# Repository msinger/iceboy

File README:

iceboy
------

http://iceboy.a-singer.de/
https://github.com/msinger/iceboy/
https://sourceforge.net/projects/iceboy/

Licensed under CERN-OHL-W v2
https://cern-ohl.web.cern.ch/

The goal of this project is to implement a GameBoy in Verilog using the open
source IceStorm tools for Lattice iCE40HX-8K FPGAs. You can get the tools from
here:
  http://www.clifford.at/icestorm/

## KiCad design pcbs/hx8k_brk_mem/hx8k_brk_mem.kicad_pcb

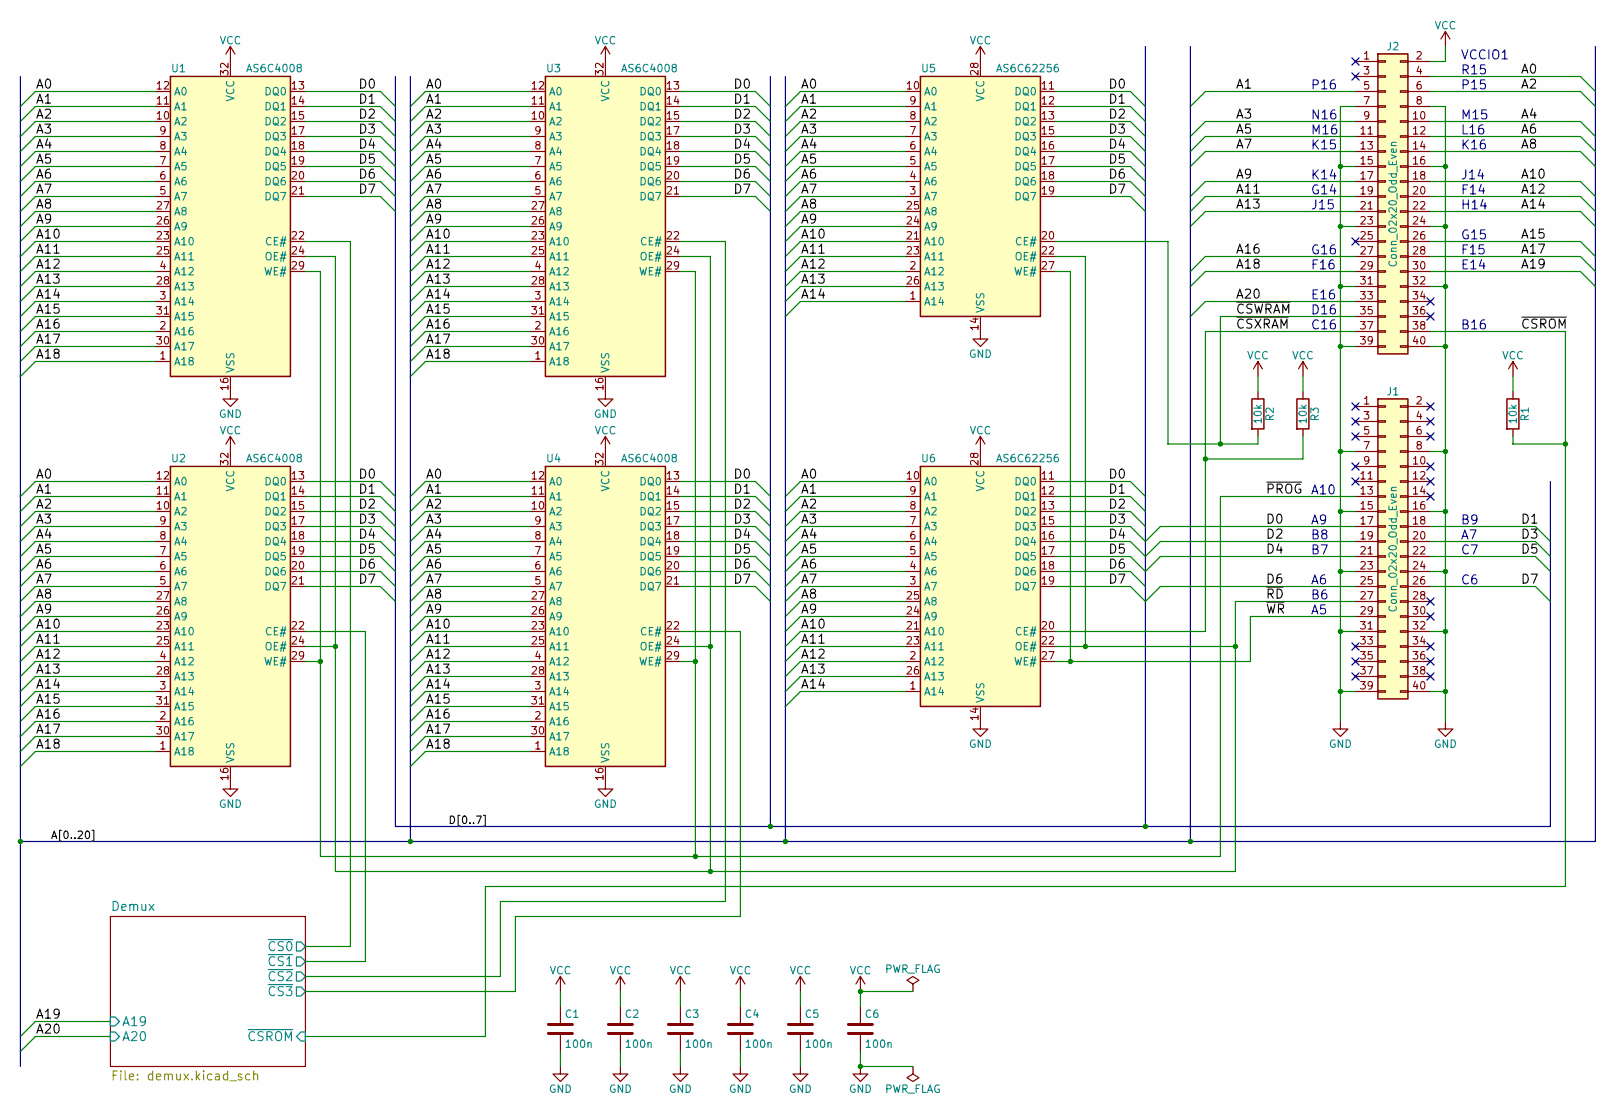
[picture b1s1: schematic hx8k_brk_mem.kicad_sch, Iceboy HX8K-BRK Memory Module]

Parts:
C1, C2, C3, C4, C5, C6: 100n; C_Disc_D3.0mm_W2.0mm_P2.50mm
J1, J2: Conn_02x20_Odd_Even; PinSocket_2x20_P2.54mm_Vertical
R1, R2, R3: 10k; R_Axial_DIN0207_L6.3mm_D2.5mm_P10.16mm_Horizontal
U1, U2, U3, U4: AS6C4008; DIP-32_W15.24mm_Socket
U5, U6: AS6C62256; DIP-28_W15.24mm_Socket

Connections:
/A0: J2.4, U1.12 (A0), U2.12 (A0), U3.12 (A0), U4.12 (A0), U5.10 (A0), U6.10 (A0)
/A1: J2.5, U1.11 (A1), U2.11 (A1), U3.11 (A1), U4.11 (A1), U5.9 (A1), U6.9 (A1)
/A2: J2.6, U1.10 (A2), U2.10 (A2), U3.10 (A2), U4.10 (A2), U5.8 (A2), U6.8 (A2)
/A3: J2.9, U1.9 (A3), U2.9 (A3), U3.9 (A3), U4.9 (A3), U5.7 (A3), U6.7 (A3)
/A4: J2.10, U1.8 (A4), U2.8 (A4), U3.8 (A4), U4.8 (A4), U5.6 (A4), U6.6 (A4)
/A5: J2.11, U1.7 (A5), U2.7 (A5), U3.7 (A5), U4.7 (A5), U5.5 (A5), U6.5 (A5)
/A6: J2.12, U1.6 (A6), U2.6 (A6), U3.6 (A6), U4.6 (A6), U5.4 (A6), U6.4 (A6)
/A7: J2.13, U1.5 (A7), U2.5 (A7), U3.5 (A7), U4.5 (A7), U5.3 (A7), U6.3 (A7)
/A8: J2.14, U1.27 (A8), U2.27 (A8), U3.27 (A8), U4.27 (A8), U5.25 (A8), U6.25 (A8)
/A9: J2.17, U1.26 (A9), U2.26 (A9), U3.26 (A9), U4.26 (A9), U5.24 (A9), U6.24 (A9)
/A10: J2.18, U1.23 (A10), U2.23 (A10), U3.23 (A10), U4.23 (A10), U5.21 (A10), U6.21 (A10)
/A11: J2.19, U1.25 (A11), U2.25 (A11), U3.25 (A11), U4.25 (A11), U5.23 (A11), U6.23 (A11)
/A12: J2.20, U1.4 (A12), U2.4 (A12), U3.4 (A12), U4.4 (A12), U5.2 (A12), U6.2 (A12)
/A13: J2.21, U1.28 (A13), U2.28 (A13), U3.28 (A13), U4.28 (A13), U5.26 (A13), U6.26 (A13)
/A14: J2.22, U1.3 (A14), U2.3 (A14), U3.3 (A14), U4.3 (A14), U5.1 (A14), U6.1 (A14)
/A15: J2.26, U1.31 (A15), U2.31 (A15), U3.31 (A15), U4.31 (A15)
/A16: J2.27, U1.2 (A16), U2.2 (A16), U3.2 (A16), U4.2 (A16)
/A17: J2.28, U1.30 (A17), U2.30 (A17), U3.30 (A17), U4.30 (A17)
/A18: J2.29, U1.1 (A18), U2.1 (A18), U3.1 (A18), U4.1 (A18)
/A19: J2.30; also elsewhere on the board
/A20: J2.33; also elsewhere on the board
/D0: J1.17, U1.13 (DQ0), U2.13 (DQ0), U3.13 (DQ0), U4.13 (DQ0), U5.11 (DQ0), U6.11 (DQ0)
/D1: J1.18, U1.14 (DQ1), U2.14 (DQ1), U3.14 (DQ1), U4.14 (DQ1), U5.12 (DQ1), U6.12 (DQ1)
/D2: J1.19, U1.15 (DQ2), U2.15 (DQ2), U3.15 (DQ2), U4.15 (DQ2), U5.13 (DQ2), U6.13 (DQ2)
/D3: J1.20, U1.17 (DQ3), U2.17 (DQ3), U3.17 (DQ3), U4.17 (DQ3), U5.15 (DQ3), U6.15 (DQ3)
/D4: J1.21, U1.18 (DQ4), U2.18 (DQ4), U3.18 (DQ4), U4.18 (DQ4), U5.16 (DQ4), U6.16 (DQ4)
/D5: J1.22, U1.19 (DQ5), U2.19 (DQ5), U3.19 (DQ5), U4.19 (DQ5), U5.17 (DQ5), U6.17 (DQ5)
/D6: J1.25, U1.20 (DQ6), U2.20 (DQ6), U3.20 (DQ6), U4.20 (DQ6), U5.18 (DQ6), U6.18 (DQ6)
/D7: J1.26, U1.21 (DQ7), U2.21 (DQ7), U3.21 (DQ7), U4.21 (DQ7), U5.19 (DQ7), U6.19 (DQ7)
/Demux/~CS0: U1.22 (CE#); also elsewhere on the board
/Demux/~CS1: U2.22 (CE#); also elsewhere on the board
/Demux/~CS2: U3.22 (CE#); also elsewhere on the board
/Demux/~CS3: U4.22 (CE#); also elsewhere on the board
/~CSROM: J2.38, R1.2; also elsewhere on the board
/~CSWRAM: J2.35, R2.2, U5.20 (CE#)
/~CSXRAM: J2.37, R3.2, U6.20 (CE#)
/~PROG: J1.13, U1.29 (WE#), U2.29 (WE#), U3.29 (WE#), U4.29 (WE#)
/~RD: J1.27, U1.24 (OE#), U2.24 (OE#), U3.24 (OE#), U4.24 (OE#), U5.22 (OE#), U6.22 (OE#)
/~WR: J1.29, U5.27 (WE#), U6.27 (WE#)
GND: C1.2, C2.2, C3.2, C4.2, C5.2, C6.2, J1.7, J1.8, J1.15, J1.16, J1.23, J1.24, J1.31, J1.32, J1.39, J1.40, J2.7, J2.8, J2.15, J2.16, J2.23, J2.24, J2.31, J2.32, J2.39, J2.40, U1.16 (VSS), U2.16 (VSS), U3.16 (VSS), U4.16 (VSS), U5.14 (VSS), U6.14 (VSS); also elsewhere on the board
VCC: C1.1, C2.1, C3.1, C4.1, C5.1, C6.1, J2.2, R1.1, R2.1, R3.1, U1.32 (VCC), U2.32 (VCC), U3.32 (VCC), U4.32 (VCC), U5.28 (VCC), U6.28 (VCC); also elsewhere on the board

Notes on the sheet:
E16
P16
VCCIO1
M15
L16
N16
C16
G16
F16
K16
F15
G14
A10
K15
D16
F14
J15
G15
J14
E14
B16
R15
K14
M16
H14
P15

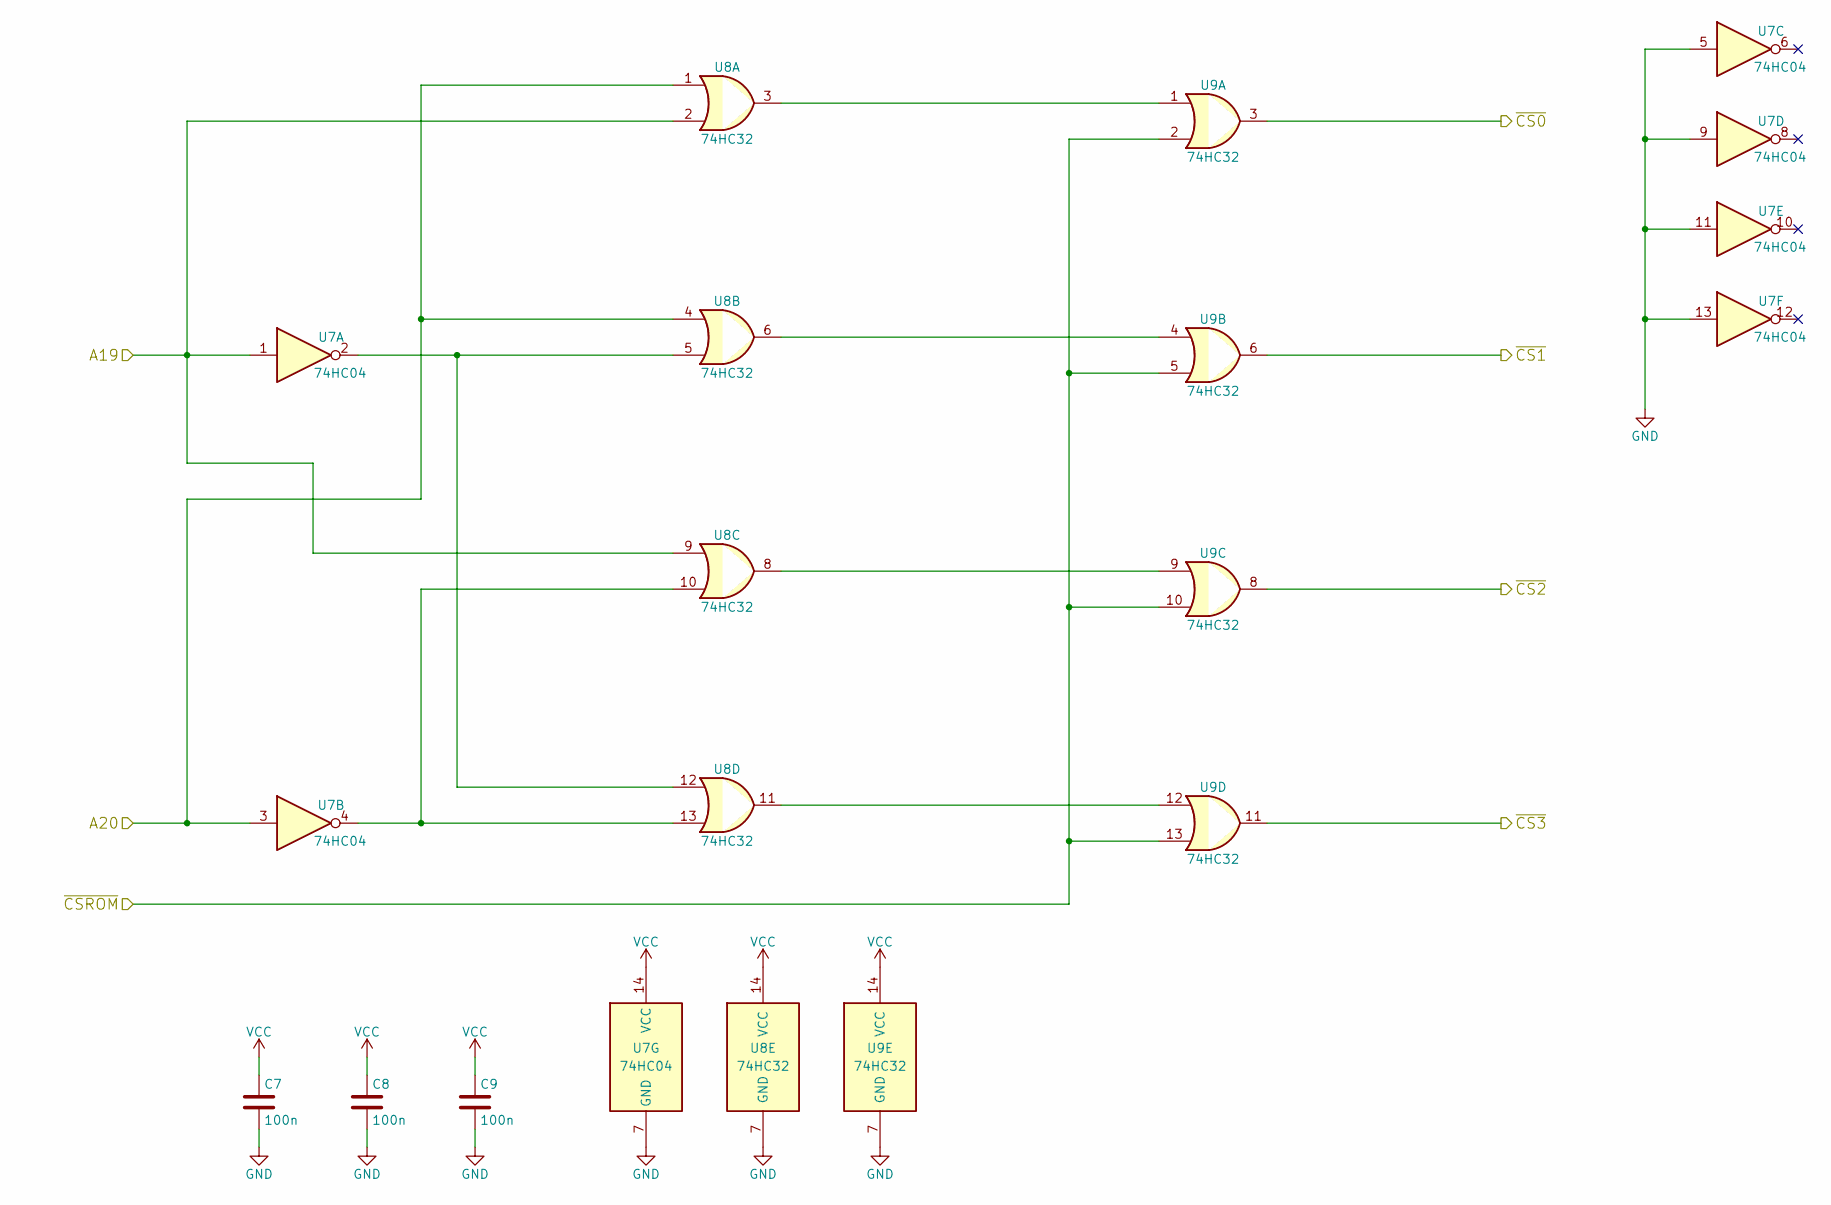
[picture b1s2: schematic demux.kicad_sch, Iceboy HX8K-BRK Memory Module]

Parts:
C7, C8, C9: 100n; C_Disc_D3.0mm_W2.0mm_P2.50mm
U7: 74HC04; DIP-14_W7.62mm_Socket
U8, U9: 74HC32; DIP-14_W7.62mm_Socket

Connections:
/A19: U7.1, U8.2, U8.9; also elsewhere on the board
/A20: U7.3, U8.1, U8.4; also elsewhere on the board
/Demux/~CS0: U9.3; also elsewhere on the board
/Demux/~CS1: U9.6; also elsewhere on the board
/Demux/~CS2: U9.8; also elsewhere on the board
/Demux/~CS3: U9.11; also elsewhere on the board
/~CSROM: U9.2, U9.5, U9.10, U9.13; also elsewhere on the board
GND: C7.2, C8.2, C9.2, U7.5, U7.7 (GND), U7.9, U7.11, U7.13, U8.7 (GND), U9.7 (GND); also elsewhere on the board
unnamed: U7.2, U8.5, U8.12
unnamed: U7.4, U8.10, U8.13
unnamed: U8.3, U9.1
unnamed: U8.6, U9.4
unnamed: U8.8, U9.9
unnamed: U8.11, U9.12
VCC: C7.1, C8.1, C9.1, U7.14 (VCC), U8.14 (VCC), U9.14 (VCC); also elsewhere on the board

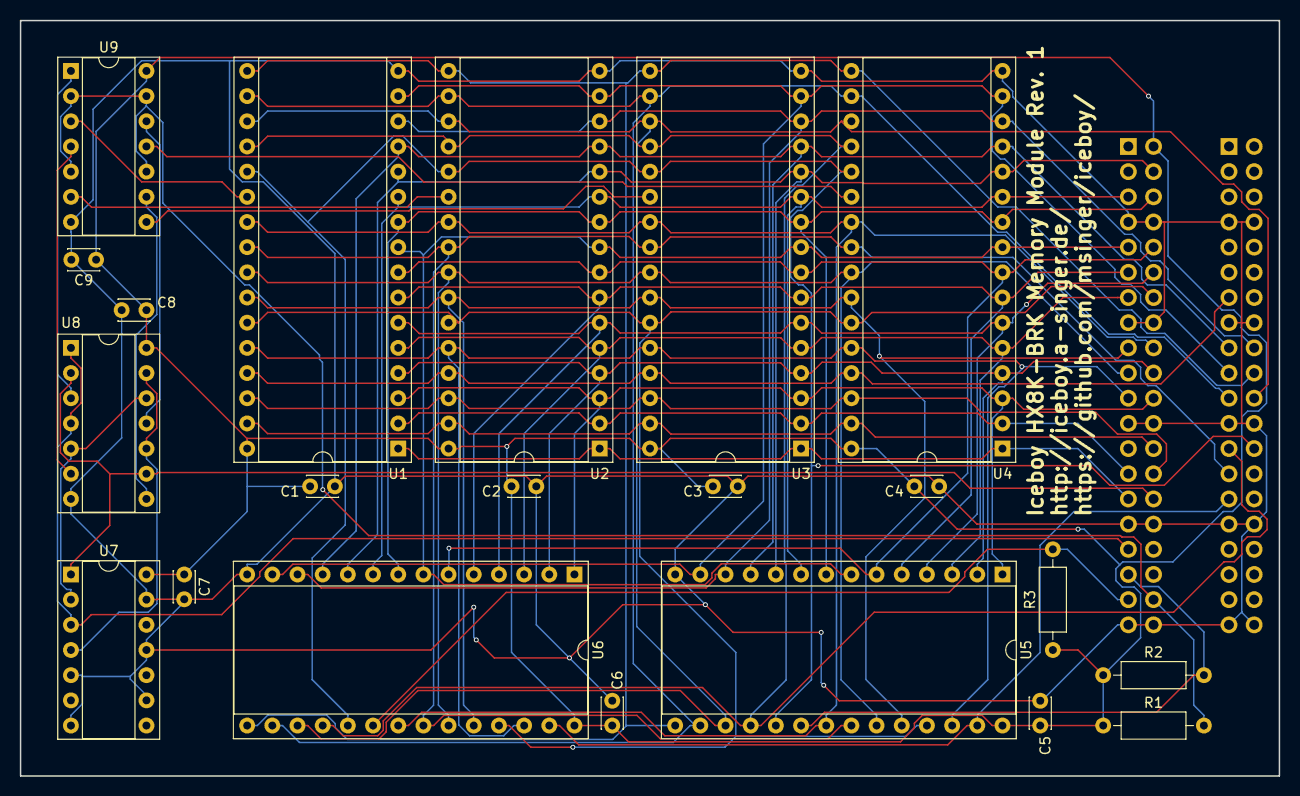
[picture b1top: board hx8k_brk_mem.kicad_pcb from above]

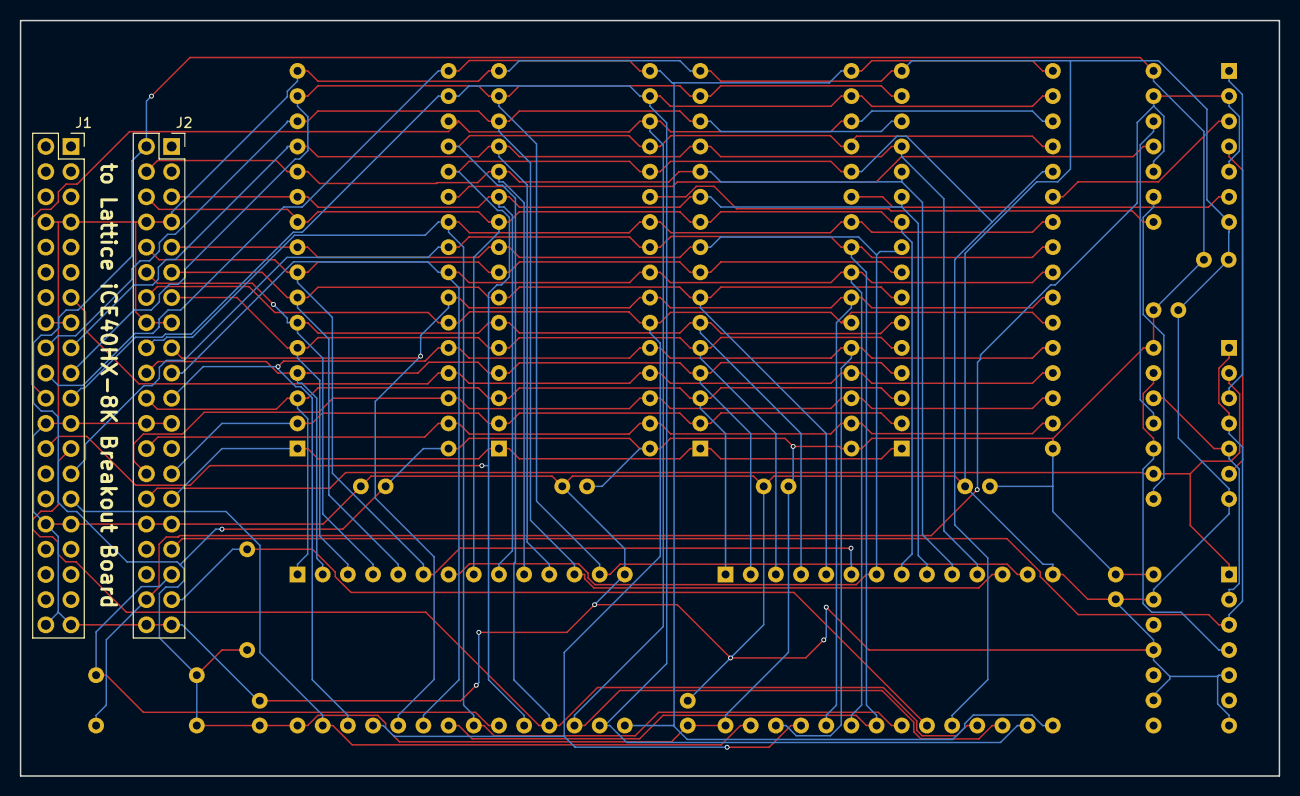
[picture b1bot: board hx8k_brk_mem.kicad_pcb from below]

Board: 2 copper layers, 127.0 x 76.2 mm, 23 parts (2 on the bottom side), 47 nets.

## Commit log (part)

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2018-01-25 add gitignore
2018-01-25 cleanup
2018-01-25 implement more jumps
2018-01-27 implemented most LD and ALU instructions
2018-01-27 implement post inc/dec indirect LD
2018-01-27 re-use 16bit adder for PC+, SP+2, rel jumps, HL+/-
2018-01-27 quiet build output
2018-01-27 implement relative jumps; fix bus timings
2018-01-28 do full 16x16 bit add for 16-bit ADD ops
2018-01-28 impl. all LD, INC, DEC and 16-bit ADD
2018-01-29 implemented PUSH, POP and indirect LD
2018-01-30 implemented RET and some misc
2018-01-31 implemented rotate/shift/swap instructions
2018-02-08 add Epson LCD init code
2018-02-10 LCD blew up -- fuck it -- look for another one
2018-02-16 add skeleton for debugger
2018-02-18 debugger works a bit
2018-02-19 small fixes and PLL
2018-02-20 implement d command for debugger
2018-02-24 debugger: breakpoints, halt, continue, step
2018-02-25 debugger works stable
2018-02-26 fix conditional relative jumps
2018-02-26 check halt when setting breakpoint
2018-03-02 fix comments
2018-03-03 reduce size
2018-03-03 fix bit swap
2018-03-03 add OAM
2018-03-04 unmapped io adresses read ff
2018-03-04 really add OAM
2018-03-04 add HRAM
2018-03-07 move ff50 from map.v to bootrom.v
2018-03-10 fix CALL timing
2018-03-11 split bus for DMA
2018-03-13 fix debugger glitch
2018-03-14 add map for I/O
2018-03-18 allow dbg uart and prog uart to coexist
2018-03-18 fix 16 bit inc/dec
2018-03-18 add bootrom.bin to .gitignore
2018-03-21 implement DIV (ff04)
2018-03-22 add IF&IE (ff0f/ffff) registers
2018-03-23 fix opcode decoding
2018-03-23 implement interrupt entry & return
2018-03-24 forgot to divide pll clock by 5
2018-03-24 implement timer counter ff05-ff07
2018-03-26 implement PWMs for sound output
2018-03-26 make TAC register 3 bit wide
2018-03-26 add NR* registers for sound
2018-03-27 constant frequency output of voice 1 working
2018-03-30 implement volume inc/dec for voice 1
2018-04-02 move PPU stuff to second device
2018-04-03 clear iflag on entry - runs Choplifter II theme
2018-04-03 add kicad schematics
2018-04-04 implement length counter
2018-04-04 implement sweep (maybe)
2018-04-04 implement noise voice
2018-04-05 implement voice 3 and wave ram
2018-04-05 reset sound registers when master_ena==0
2018-04-05 implement dummy serial io port
2018-04-05 implement p1 / joypad
2018-04-05 fix ff03 in iomap
2018-04-08 implement HALT instruction
2018-04-08 implement STOP instruction
2018-04-09 UltraChip UC1611 Display init works somehow
2018-04-14 ppu stuff
2018-04-15 send pixels to uc1611
2018-04-15 implement ppu access to oam&vram
2018-04-16 some tiles display correctly
2018-04-18 fix PPU FIFO direction: shift out MSB
2018-04-18 quick workaround for vram glitch
2018-04-18 fix lcd pixel output
2018-04-23 fix glitchy wires
2018-04-24 fix glitchy memories
2018-04-25 PPU works good enough for running test ROMs
2018-04-27 fixed carry flags of 16bit instructions
2018-04-27 fix stack pointer decrement for RST
2018-04-27 fix SLA
2018-04-27 fix RES & SET for (HL)
2018-04-27 fix RL & RR for (HL)
2018-04-28 increase data hold time for ext busses
2018-04-29 fix nonreadable bits in sound registers
2018-04-29 fix X scroll
2018-04-29 implement window
2018-04-30 fix timer
    * DIV reset prevents TIMA increments
    * toggling TIMA enable can trigger TIMA increments
2018-05-01 improve PPU timing
2018-05-02 sync sound to DIV register
2018-05-04 fix MBC
2018-05-05 keep SIO clock running
2018-05-05 implement OAM DMA
2018-05-06 most of the sprite work is done
2018-05-06 fix OAM DMA timing
2018-05-06 sprites are working w/o transparency
2018-05-06 implement mixing of bg and sprite pixels
2018-05-07 tried fixing timer timing
2018-05-11 clear display RAM on init
2018-05-11 center screen
2018-05-11 clear OAM on reset
2018-06-18 remap display pins
2018-10-12 add make target for ice40_viewer
2018-10-12 move files into sub directory
2018-10-12 fix path to ice40_viewer
2018-10-13 build with autotools
2018-10-13 add configuration options
2018-10-14 add config opts for debugger and loader
2018-10-14 fix make distcheck
2018-10-31 add mem access pattern doc
2018-11-11 move docs/tests to reveng repository
2018-11-11 fix DMG model in test results
2018-12-09 switch to nextpnr
2018-12-09 fix MBC1 implementation
2019-03-03 remove unused wires
2019-03-03 fix warnings
2019-03-04 make MBC1 memory size configurable
2019-03-04 hack for passing MBC1 tests
    Tests that check if CPU reads 0xff from cartridge memory when SRAM is
    disabled in MBC fail. Maybe because the pull-up resistors are too
    weak. This commit is a temporary fix for that.
    Also needed to remove n_emu_mbc pin. Arachne and nextpnr where not able
    to route anymore.
2019-03-31 make MBC emulation configurable
2019-03-31 basic support for gbreveng board
2019-03-31 UART support for gbreveng board
2019-03-31 fix undefined WRAM address lines
2019-03-31 support onboard RAMs on gbreveng board
    - WRAM
    - onboard cartridge ROM
    - onboard cartridge RAM
2019-03-31 implement bi-directional reset pin on cart. slot
2019-03-31 output 1 MiHz clock on cartridge slot
2019-03-31 disable pull-ups on reset and emu_mbc pins
    they have external pull-downs
2019-03-31 generate !OE and DIR signals for cart. slot
2019-04-02 fix reset
2019-04-03 use 16 MiHz clock
    Now synchronization between clock domains is an issue. Debugger won't
    work anymore.
2019-04-03 don't use PLL on gbreveng board
2019-04-05 sync clock domains for prog loader
2019-04-06 dummy implementation for Sharp LH5076 & LH5077 drv
2019-04-06 make gbreveng board the default
2019-04-06 fix clock sync for prog_loader on hx8k_brk
2019-10-13 original LH507x LCD row&column drivers working
    Need to rewrite parts of UC1611 LCD driver now to
    make it work with the modified PPU signals.
2019-10-13 UC1611 LCD driver now works with new PPU signals
2019-10-13 shorten magic delays
2019-10-13 fix UC1611 LCD driver
2019-10-14 never reset two LSBs of DIV
2019-10-14 fix UC1611 LCD driver
    Lines were offset by one and last two lines were repeated as garbage at
    the end of the picture.
    rd_pxcnt needed to be sampled one tick later. It still had the previous
    value.
2019-10-26 extract UART from loader and debugger into module
2019-10-26 add clock constraints
2019-10-28 implementation for FT245 interface
2019-10-28 fix clock domain crossings for UART
    no magic delays anymore
2019-10-29 implement lock/unlock sequences for debugger
    When using FT245 interface, debugger always receives 0x00 (HALT) command
    directly after plugging in USB to a host controller. This is probably
    sent by some driver, because it does not happen when plugging into a USB
    power adapter or power bank.
    Now debugger is 'locked' on startup. All state-changing commands are
    inaccessible until an unlock sequence was received.
2019-11-03 fix clock domain crossings
2019-11-03 cleanup/unify names and interfaces
2019-11-03 implement bare minimum boot rom
2019-11-08 fix pin name
2020-04-10 fix underscores in number literals
2020-06-17 add support for HX8K_BRK memory module
2020-09-06 fix include paths for out of tree build
2020-09-06 implement Z80ish ALU
2020-09-06 fix make dist
2020-09-06 implement tests for new ALU
2020-09-06 fix usage comment for ALU
2020-09-06 use anyseq instead of don't care values in tests
2020-09-06 add ALU tests for xor, and, or, neg & cpl
2020-09-08 tests for ALU shift operations
2020-09-08 test for ALU swap operation
2020-09-14 fix usage comment for ALU bit operations
2020-09-20 remove workaround for bad yosys
    needs yosys version with commit 59c4ad8 reverted
2021-01-04 fix ppu tasks for new yosys version
2021-01-17 reworked ALU based on A-Z80 circuit
2021-01-17 Implement base for new CPU
2021-01-17 Simulate new CPU with code by yosys write_cxxrtl
2021-02-21 SM83: Add more instruction dummies
2021-02-21 SM83: Implement more LD instructions
2021-02-21 Change timings, control signals, adr incrementer
2021-02-21 SM83: Implement HL increment/decrement load instr.
2021-02-21 SM83: Implement shift/rotate instructions
2021-02-21 SM83: Remove unused or duplicate signals
2021-02-21 SM83: Move common signal patterns into tasks
2021-02-21 SM83: Add tests for 16 bit load instructions
2021-02-21 SM83: Remove second address latch WE signal
2021-02-21 SM83: Fix relative jumps duplicating high byte
2021-02-21 SM83: Fix cond. call/return instructions
2021-02-21 SM83: Fix RST opcodes
2021-02-21 SM83: Implement jump instructions (JP, JR)
2021-02-21 SM83: Add tests for 16 bit arithmetical instructions
2021-02-21 SM83: Implement basic 16 bit load instructions
2021-02-21 SM83: Port debug interface for new CPU
2021-02-21 SM83: Fix data out timing
2021-02-21 Build simulation code only on "make check"
2021-02-21 SM83: Fix carry after DAA
2021-02-21 SM83: Change two ALU signals name and polarity
    The names they use in the A-Z80 projects just make more sense.
2021-02-21 SM83: Fix zero flag for LDHL and "ADD SP, e"
2021-02-21 SM83: Implement PUSH and POP
2021-02-21 Split up formal ALU tests into smaller .sby files
2021-02-21 SM83: Fix unique case uniqueness
2021-02-21 SM83: Zero upper address lines after each mem cyc
2021-02-21 SM83: Implement 16 bit increment/decrement instr.
2021-02-21 SM83: Implement CPL and DAA instructions
2021-02-21 SM83: Name instr. according to 1996 Sharp Databook
2021-02-21 SM83: Add WZ register as preparation for JP instr.
2021-02-21 SM83: Add tests for jump instructions
2021-02-21 Add test for simulated CPU
2021-02-21 SM83: Fix "LD A, (BC)" and "LD A, (DE)"
2021-02-21 SM83: Add tests for 8 bit ALU operations
2021-02-21 SM83: Fix LD (HL), n
2021-02-21 SM83: Implement call instructions
2021-02-21 SM83: Implement all 16 bit load instructions
2021-02-21 SM83: Implement simulation for debug interface
2021-02-21 SM83: Add debugger ports to CPU
2021-02-21 SM83: Fix formal tests for new ALU
2021-02-21 SM83: Implement SCF and CCF instructions
2021-02-21 SM83: Add dummies for remaining instructions
2021-02-21 Use $anyconst in formal ALU tests
2021-02-21 SM83: Implement SWAP instruction
2021-02-21 Don't generate PHI signal in CPU
    Instead CPU cycle gets synchronized to PHI by an CPU external signal.
2021-02-21 SM83: Fix 8 bit inc/dec
2021-02-21 SM83: Change register write timing for load instr.
    ALU operations require register write on T2. Do register write for load
    operations on T2 too.
2021-02-21 SM83: Fix carry logic for SUB, SBC and CP
2021-02-21 SM83: Fix "LD (nn), SP" instruction
2021-02-21 SM83: Implement 8 bit ALU instructions (A, r)
2021-02-21 Add more tests for 8 bit load instructions
2021-02-21 SM83: Rework control structure
2021-02-21 SM83: Add tests for rotate/shift instructions
2021-02-21 SM83: Implelent all 8 bit load instructions
2021-02-21 SM83: Implement BIT instruction
2021-02-21 Simulated CPU executes code from stdin
2021-02-21 SM83: Initialize AF for add16 tests
2021-02-21 SM83: Fix carry output of SRA
2021-02-21 SM83: Implement all 16 bit arith. and logic instr.
2021-02-21 SM83: Remove low nibble from register F
2021-02-21 SM83: Fix high nibble result of "ADD SP, e"
2021-02-21 SM83: Move SP to address bus side of reg file
2021-02-21 SM83 sim: Make output parsable
2021-02-21 Copy CPU debug interface before adapting for SM83
2021-02-21 Make SM83 sim configurable with cmdline options
2021-02-21 SM83: Add tests for call/return instructions
2021-02-21 Fix "make clean" for sim subdir
2021-02-21 SM83: Add tests for bit manipulation instructions
2021-02-21 SM83: Add tests for CPL and DAA instructions
2021-02-21 Add option to SM83 sim for dumping memory
2021-02-21 SM83: Disallow interrupts after CB prefix
2021-02-21 Collect shell functions for tests in new file
2021-02-21 Move some tests into sub folder
2021-02-21 Remove HW tests for old ALU
2021-03-07 Add formal tests for load instructions
2021-03-07 SM83: Fix logic loops detected by new yosys
2021-03-07 Generate sby files for formal ALU tests
2021-03-14 Fix debug ifc simulation
2021-03-14 SM83: Fix debug interface for new CPU
2021-03-15 Convert to SystemVerilog
2021-08-18 Switch to CERN-OHL-W v2 license
2022-11-20 Cleanup github language stats
2024-06-20 Migrate memory pcb from KiCad 4 to KiCad 8
